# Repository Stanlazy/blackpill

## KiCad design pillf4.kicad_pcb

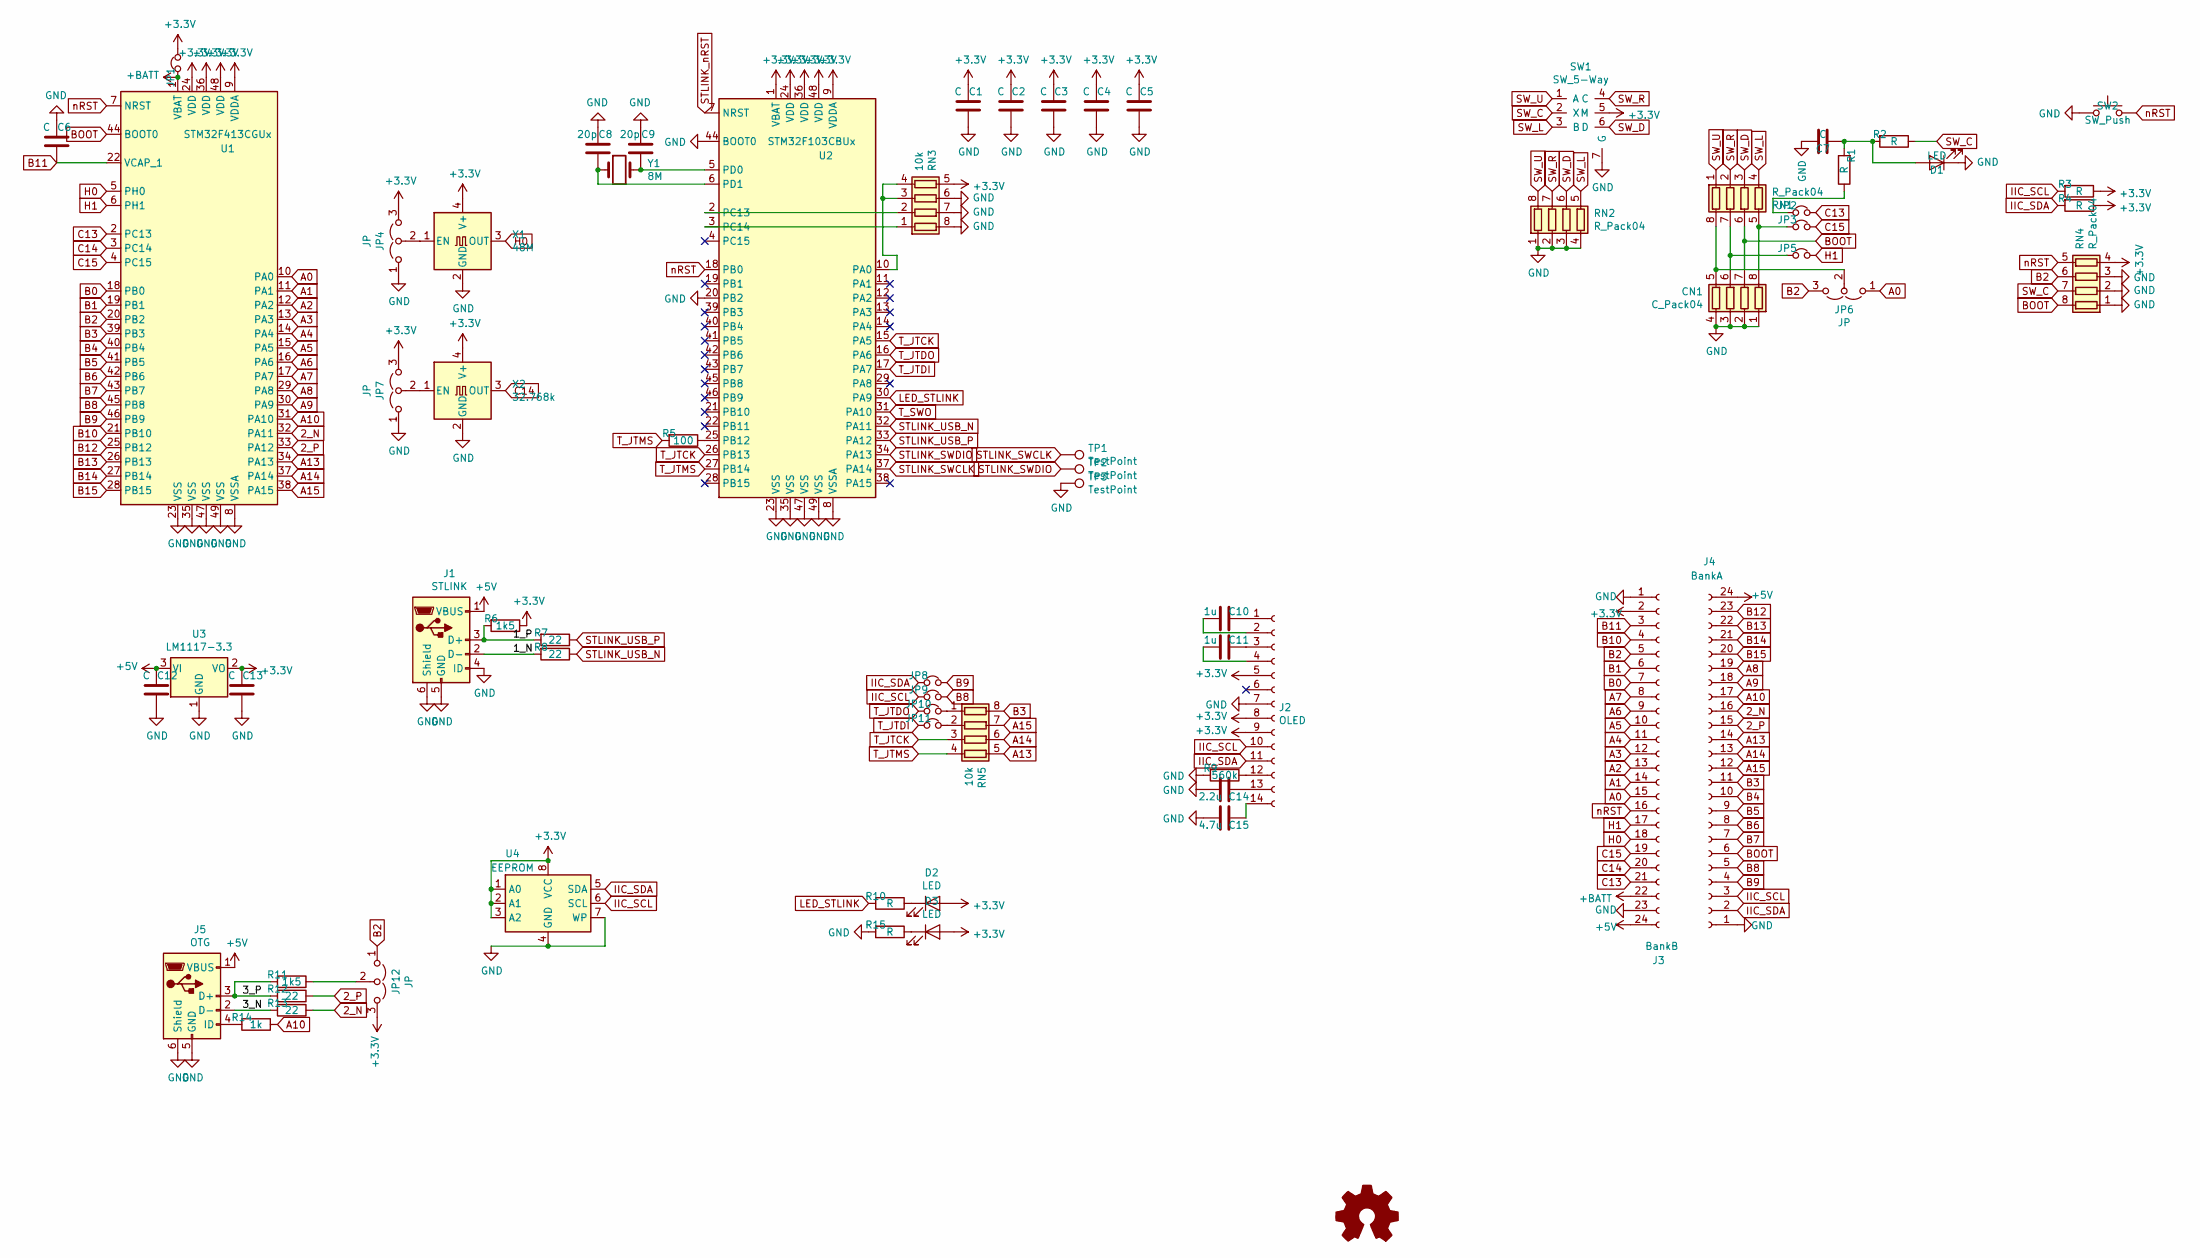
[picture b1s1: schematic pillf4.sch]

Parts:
C1, C2, C3, C4, C5, C6, C7: C; C_0603_1608Metric
C8, C9: 20p; C_0402_1005Metric
C10, C11: 1u; C_0603_1608Metric
C12, C13: C; C_1206_3216Metric
C14: 2.2u; C_0603_1608Metric
C15: 4.7u; C_0603_1608Metric
CN1: C_Pack04; R_Array_Concave_4x0402
D1, D2, D3: LED; LED_0603_1608Metric
J1: STLINK; USB_Micro-B_Molex-105017-0001
J2: OLED; OLED_Solder_1x14_P0.62
J3: BankB; PinHeader_1x24_P2.54mm_Vertical
J4: BankA; PinHeader_1x24_P2.54mm_Vertical
J5: OTG; USB_Micro-B_Molex-105017-0001
JP1, JP2, JP3, JP5, JP8, JP9, JP10, JP11: jmp; SolderJumper-2_P0.7mm
JP4, JP6, JP7, JP12: JP; SolderJumper-3_P0.7mm
LOGO1: Logo_Open_Hardware_Small; stanlazy_7.2mm
R1, R2, R3, R4, R10, R15: R; R_0402_1005Metric
R5: 100; R_0402_1005Metric
R6, R11: 1k5; R_0402_1005Metric
R7, R8, R12, R13: 22; R_0402_1005Metric
R9: 560k; R_0402_1005Metric
R14: 1k; R_0402_1005Metric
RN1, RN2, RN4: R_Pack04; R_Array_Concave_4x0402
RN3, RN5: 10k; R_Array_Concave_4x0402
SW1: SW_5-Way; SW_5-Way_7.5x7.5mm
SW2: SW_Push; SW_Push_3x6mm
TP1, TP2, TP3: TestPoint; TestPoint_Pad_D1.0mm
U1: STM32F413CGUx; QFN-48-1EP_7x7mm_P0.5mm_EP3x3mm
U2: STM32F103CBUx; QFN-48_7x7mm_P0.5mm
U3: LM1117-3.3; SOT-89-3
U4: EEPROM; DFN-8_3x2mm_P0.5mm
X1: 48M; Crystal_SMD_2016-4Pin_2.0x1.6mm_HandSoldering
X2: 32.768k; Crystal_SMD_2016-4Pin_2.0x1.6mm_HandSoldering
Y1: 8M; Crystal_SMD_3215-2Pin_3.2x1.5mm_HandSoldering

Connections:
2_N: J4.16, R13.1, U1.32 (PA11)
2_P: J4.15, R12.1, U1.33 (PA12)
+3V3: C1.1, C2.1, C3.1, C4.1, C5.1, C13.1, D2.2 (A), D3.2 (A), J2.5, J2.8, J2.9, J3.2, JP1.2, JP4.3 (B), JP7.3 (B), JP12.3 (B), R3.1, R4.1, R6.1, RN3.5 (R4.2), RN4.4 (R4.1), SW1.5 (M), U1.9 (VDDA), U1.24 (VDD), U1.36 (VDD), U1.48 (VDD), U2.1 (VBAT), U2.9 (VDDA), U2.24 (VDD), U2.36 (VDD), U2.48 (VDD), U3.2 (VO), U4.1 (A0), U4.2 (A1), U4.3 (A2), U4.8 (VCC), X1.4 (V+), X2.4 (V+)
+5V: C12.1, J1.1 (VBUS), J3.24, J4.24, J5.1 (VBUS), U3.3 (VI)
+BATT: J3.22, JP1.1, U1.1 (VBAT)
/1_N: J1.2 (D-), R8.2
/1_P: J1.3 (D+), R6.2, R7.2
/3_N: J5.2 (D-), R13.2
/3_P: J5.3 (D+), R11.2, R12.2
A0: J3.15, JP6.1 (A), U1.10 (PA0)
A1: J3.14, U1.11 (PA1)
A2: J3.13, U1.12 (PA2)
A3: J3.12, U1.13 (PA3)
A4: J3.11, U1.14 (PA4)
A5: J3.10, U1.15 (PA5)
A6: J3.9, U1.16 (PA6)
A7: J3.8, U1.17 (PA7)
A8: J4.19, U1.29 (PA8)
A9: J4.18, U1.30 (PA9)
A10: J4.17, R14.1, U1.31 (PA10)
A13: J4.14, RN5.5 (R4.2), U1.34 (PA13)
A14: J4.13, RN5.6 (R3.2), U1.37 (PA14)
A15: J4.12, RN5.7 (R2.2), U1.38 (PA15)
B0: J3.7, U1.18 (PB0)
B1: J3.6, U1.19 (PB1)
B2: J3.5, JP6.3 (B), JP12.1 (A), RN4.6 (R3.2), U1.20 (PB2)
B3: J4.11, RN5.8 (R1.2), U1.39 (PB3)
B4: J4.10, U1.40 (PB4)
B5: J4.9, U1.41 (PB5)
B6: J4.8, U1.42 (PB6)
B7: J4.7, U1.43 (PB7)
B8: J4.5, JP9.2, U1.45 (PB8)
B9: J4.4, JP8.2, U1.46 (PB9)
B10: J3.4, U1.21 (PB10)
B11: C6.1, J3.3, U1.22 (VCAP_1)
B12: J4.23, U1.25 (PB12)
B13: J4.22, U1.26 (PB13)
B14: J4.21, U1.27 (PB14)
B15: J4.20, U1.28 (PB15)
BOOT: CN1.7 (R2.2), J4.6, RN1.6 (R3.2), RN4.8 (R1.2), U1.44 (BOOT0)
C13: J3.21, JP2.2, U1.2 (PC13)
C14: J3.20, U1.3 (PC14), X2.3 (OUT)
C15: J3.19, JP3.2, U1.4 (PC15)
GND: C1.2, C2.2, C3.2, C4.2, C5.2, C6.2, C7.1, C8.2, C9.2, C12.2, C13.2, C14.2, C15.2, CN1.1 (R1.1), CN1.2 (R2.1), CN1.3 (R3.1), CN1.4 (R4.1), D1.1 (K), J1.4 (ID), J1.5 (GND), J1.6 (Shield), J2.7, J3.1, J3.23, J4.1, J5.5 (GND), J5.6 (Shield), JP4.1 (A), JP7.1 (A), R9.2, R15.2, RN2.1 (R1.1), RN2.2 (R2.1), RN2.3 (R3.1), RN2.4 (R4.1), RN3.6 (R3.2), RN3.7 (R2.2), RN3.8 (R1.2), RN4.1 (R1.1), RN4.2 (R2.1), RN4.3 (R3.1), SW1.7 (G), SW2.1, TP3.1, U1.8 (VSSA), U1.23 (VSS), U1.35 (VSS), U1.47 (VSS), U1.49 (VSS), U2.8 (VSSA), U2.20 (PB2), U2.23 (VSS), U2.35 (VSS), U2.44 (BOOT0), U2.47 (VSS), U2.49 (VSS), U3.1 (GND), U4.4 (GND), U4.7 (WP), X1.2 (GND), X2.2 (GND)
H0: J3.18, U1.5 (PH0), X1.3 (OUT)
H1: J3.17, JP5.2, U1.6 (PH1)
IIC_SCL: J2.10, J4.3, JP9.1, R3.2, U4.6 (SCL)
IIC_SDA: J2.11, J4.2, JP8.1, R4.2, U4.5 (SDA)
LED_STLINK: R10.2, U2.30 (PA9)
unnamed: C7.2, D1.2 (A), R1.2, R2.2
unnamed: C8.1, U2.6 (PD1), Y1.1
unnamed: C9.1, U2.5 (PD0), Y1.2
unnamed: C10.1, J2.1
unnamed: C10.2, J2.2
unnamed: C11.1, J2.3
unnamed: C11.2, J2.4
unnamed: C14.1, J2.13
unnamed: C15.1, J2.14
unnamed: CN1.5 (R4.2), JP6.2 (C), RN1.8 (R1.2)
unnamed: CN1.6 (R3.2), JP5.1, RN1.7 (R2.2)
unnamed: CN1.8 (R1.2), JP3.1, RN1.5 (R4.2)
unnamed: D2.1 (K), R10.1
unnamed: D3.1 (K), R15.1
unnamed: J2.12, R9.1
unnamed: J5.4 (ID), R14.2
unnamed: JP2.1, R1.1
unnamed: JP4.2 (C), X1.1 (EN)
unnamed: JP7.2 (C), X2.1 (EN)
unnamed: JP10.2, RN5.1 (R1.1)
unnamed: JP11.2, RN5.2 (R2.1)
unnamed: JP12.2 (C), R11.1
unnamed: R5.1, U2.25 (PB12)
unnamed: RN3.1 (R1.1), U2.3 (PC14)
unnamed: RN3.2 (R2.1), U2.2 (PC13)
unnamed: RN3.3 (R3.1), RN3.4 (R4.1), U2.10 (PA0)
STLINK_SWCLK: TP1.1, U2.37 (PA14)
STLINK_SWDIO: TP2.1, U2.34 (PA13)
STLINK_USB_N: R8.1, U2.32 (PA11)
STLINK_USB_P: R7.1, U2.33 (PA12)
SW_C: R2.1, RN4.7 (R2.2), SW1.2 (X)
SW_D: RN1.3 (R3.1), RN2.6 (R3.2), SW1.6 (D)
SW_L: RN1.4 (R4.1), RN2.5 (R4.2), SW1.3 (B)
SW_R: RN1.2 (R2.1), RN2.7 (R2.2), SW1.4 (C)
SW_U: RN1.1 (R1.1), RN2.8 (R1.2), SW1.1 (A)
T_JTCK: RN5.3 (R3.1), U2.15 (PA5), U2.26 (PB13)
T_JTDI: JP11.1, U2.17 (PA7)
T_JTDO: JP10.1, U2.16 (PA6)
T_JTMS: R5.2, RN5.4 (R4.1), U2.27 (PB14)
nRST: J3.16, RN4.5 (R4.2), SW2.2, U1.7 (NRST), U2.18 (PB0)

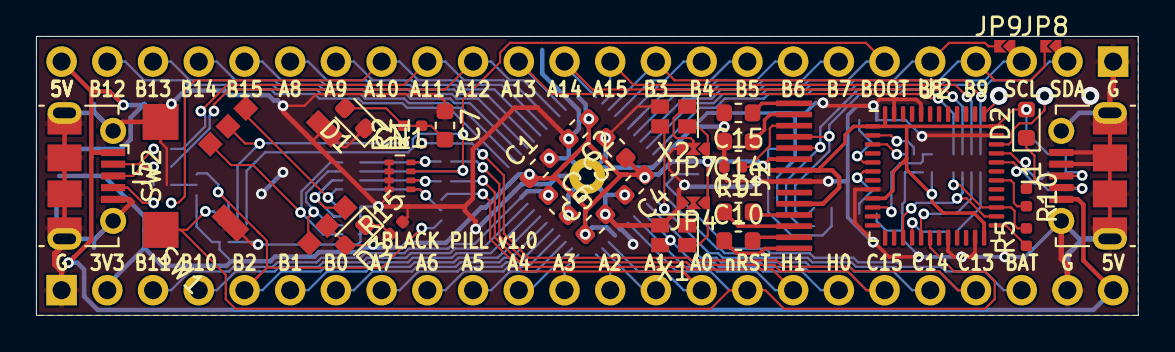
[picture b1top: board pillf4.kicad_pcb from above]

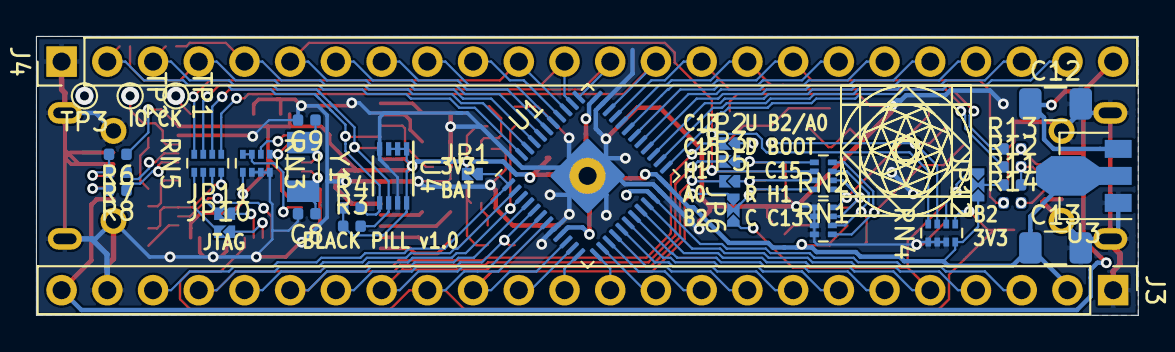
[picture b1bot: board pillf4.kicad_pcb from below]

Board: 2 copper layers, 61.2 x 15.5 mm, 69 parts (36 on the bottom side), 89 nets.

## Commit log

2019-08-07 upload v1.0
